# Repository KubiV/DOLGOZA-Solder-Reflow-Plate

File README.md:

# Dolgoza
## DIY Solder Reflow Plate

   DIY Solder Reflow Plate easy to assamble - mainly THT components, relatively large SMD components easy to solder using soldering iron.

Derived from: https://github.com/AfterEarthLTD/Solder-Reflow-Plate

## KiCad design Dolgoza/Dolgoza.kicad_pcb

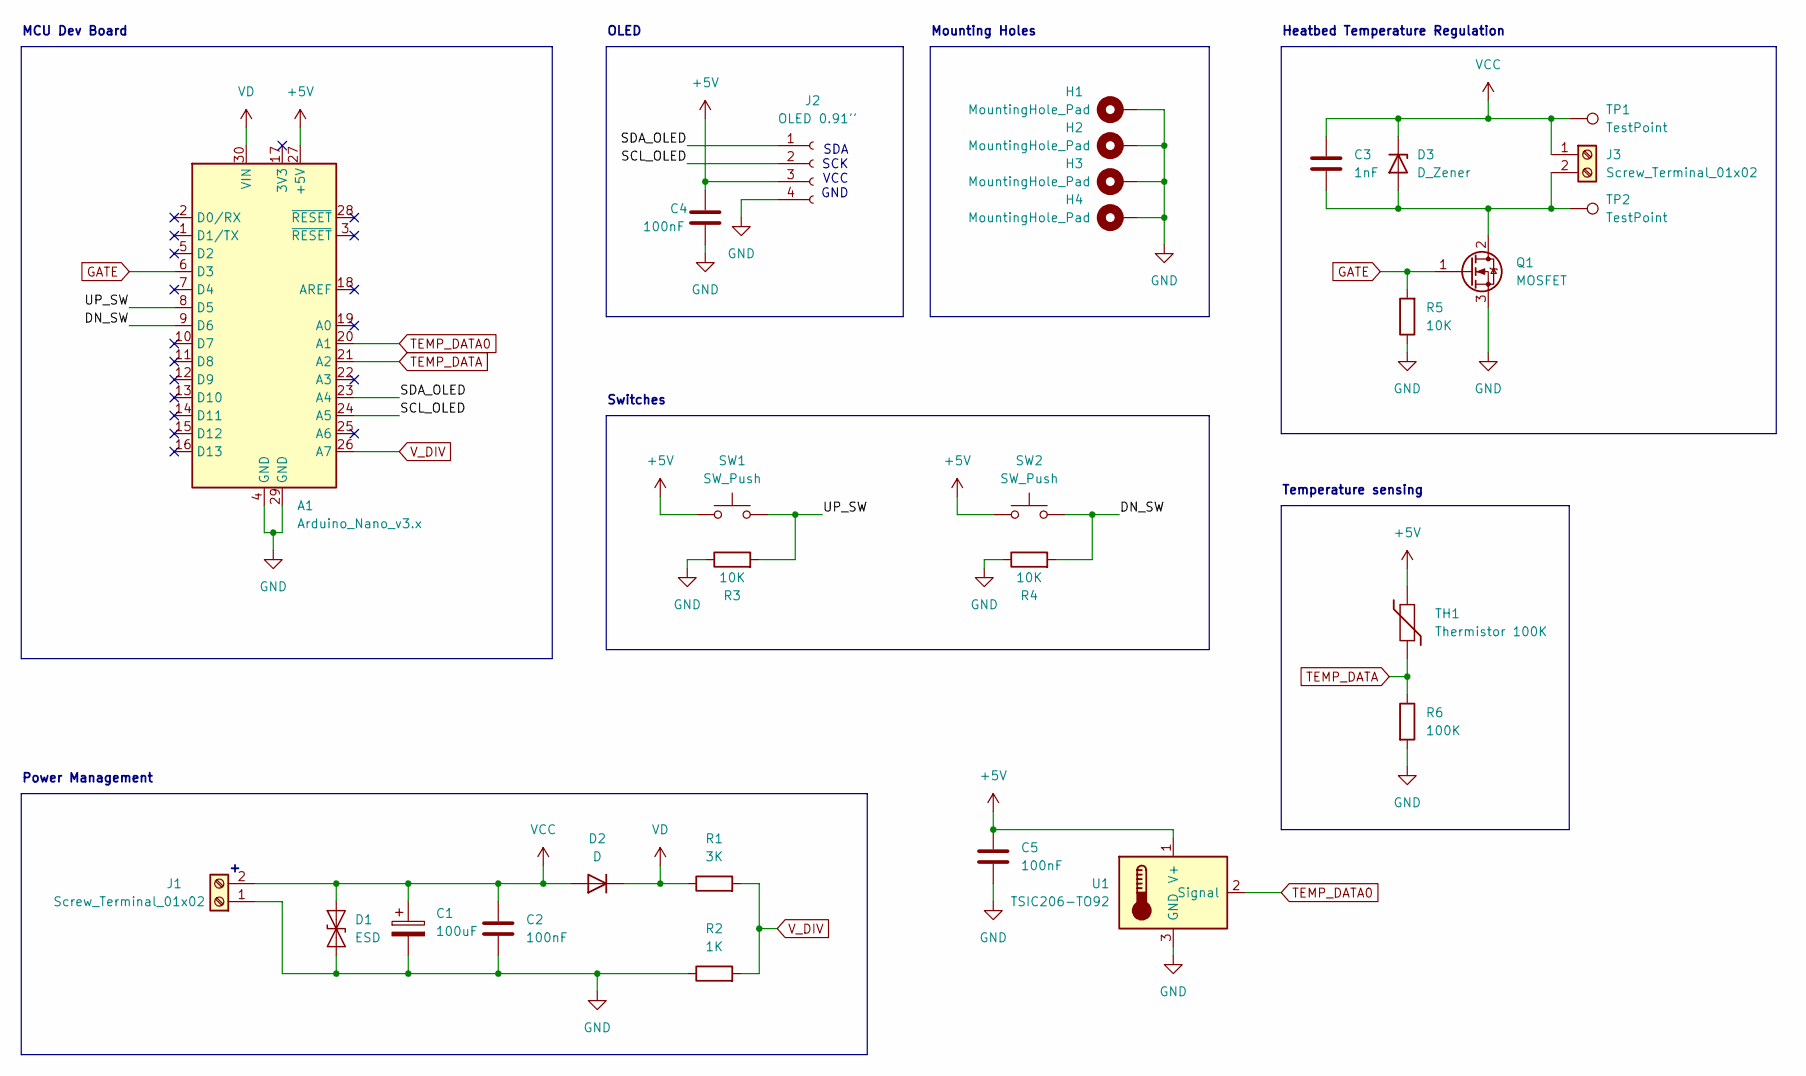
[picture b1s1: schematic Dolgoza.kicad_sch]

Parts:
A1: Arduino_Nano_v3.x; Arduino_Nano
C1: 100uF; CP_Elec_8x5.4
C2, C4, C5: 100nF; C_0805_2012Metric
C3: 1nF; C_0805_2012Metric
D1: ESD; D_DO-15_P12.70mm_Horizontal
D2: D; D_DO-41_SOD81_P10.16mm_Horizontal
D3: D_Zener; D_DO-41_SOD81_P10.16mm_Horizontal
H1, H2, H3, H4: MountingHole_Pad; MountingHole_3.2mm_M3_DIN965_Pad
J1, J3: Screw_Terminal_01x02; TerminalBlock_bornier-2_P5.08mm
J2: OLED 0.91''; PinHeader_1x04_P2.54mm_Vertical
Q1: MOSFET; TO-220-3_Vertical
R1: 3K; R_0805_2012Metric
R2: 1K; R_0805_2012Metric
R3, R4, R5: 10K; R_0805_2012Metric
R6: 100K; R_0805_2012Metric
SW1, SW2: SW_Push; SW_PUSH_6mm
TH1: Thermistor 100K; PinHeader_1x02_P2.54mm_Vertical
TP1, TP2: TestPoint; TestPoint_Pad_3.0x3.0mm
U1: TSIC206-TO92; PinHeader_1x03_P2.54mm_Vertical

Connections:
+5V: A1.27 (+5V), C4.1, C5.1, J2.3, SW1.1, SW2.1, TH1.2, U1.1 (V+)
/DN_SW: A1.9 (D6), R4.2, SW2.2
/SCL_OLED: A1.24 (A5), J2.2
/SDA_OLED: A1.23 (A4), J2.1
/UP_SW: A1.8 (D5), R3.2, SW1.2
GATE: A1.6 (D3), Q1.1 (G), R5.2
GND: A1.4 (GND), A1.29 (GND), C1.2, C2.2, C4.2, C5.2, D1.1 (A1), H1.1, H2.1, H3.1, H4.1, J1.1, J2.4, Q1.3 (S), R2.1, R3.1, R4.1, R5.1, R6.2, U1.3 (GND)
unnamed: C3.2, D3.2 (A), J3.2, Q1.2 (D), TP2.1
TEMP_DATA: A1.21 (A2), R6.1, TH1.1
TEMP_DATA0: A1.20 (A1), U1.2 (Signal)
VCC: C1.1, C2.1, C3.1, D1.2 (A2), D2.2 (A), D3.1 (K), J1.2, J3.1, TP1.1
VD: A1.30 (VIN), D2.1 (K), R1.1
V_DIV: A1.26 (A7), R1.2, R2.2

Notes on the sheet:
Temperature sensing
Mounting Holes
OLED
Heatbed Temperature Regulation
Power Management
MCU Dev Board
SDA SCK VCC GND
Switches

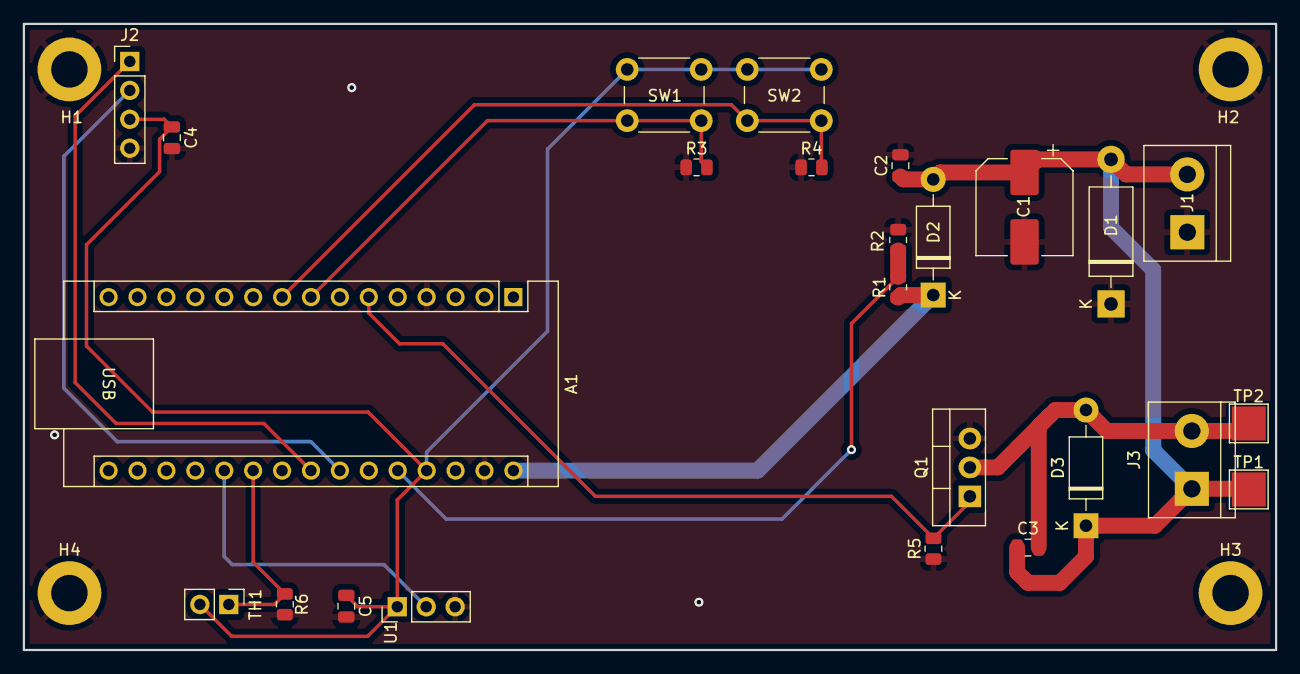
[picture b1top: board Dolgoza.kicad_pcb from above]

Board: 2 copper layers, 110.0 x 55.0 mm, 29 parts (0 on the bottom side), 13 nets.

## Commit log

2023-03-05 readme
2023-03-07 pcb text
2023-11-26 bom images
